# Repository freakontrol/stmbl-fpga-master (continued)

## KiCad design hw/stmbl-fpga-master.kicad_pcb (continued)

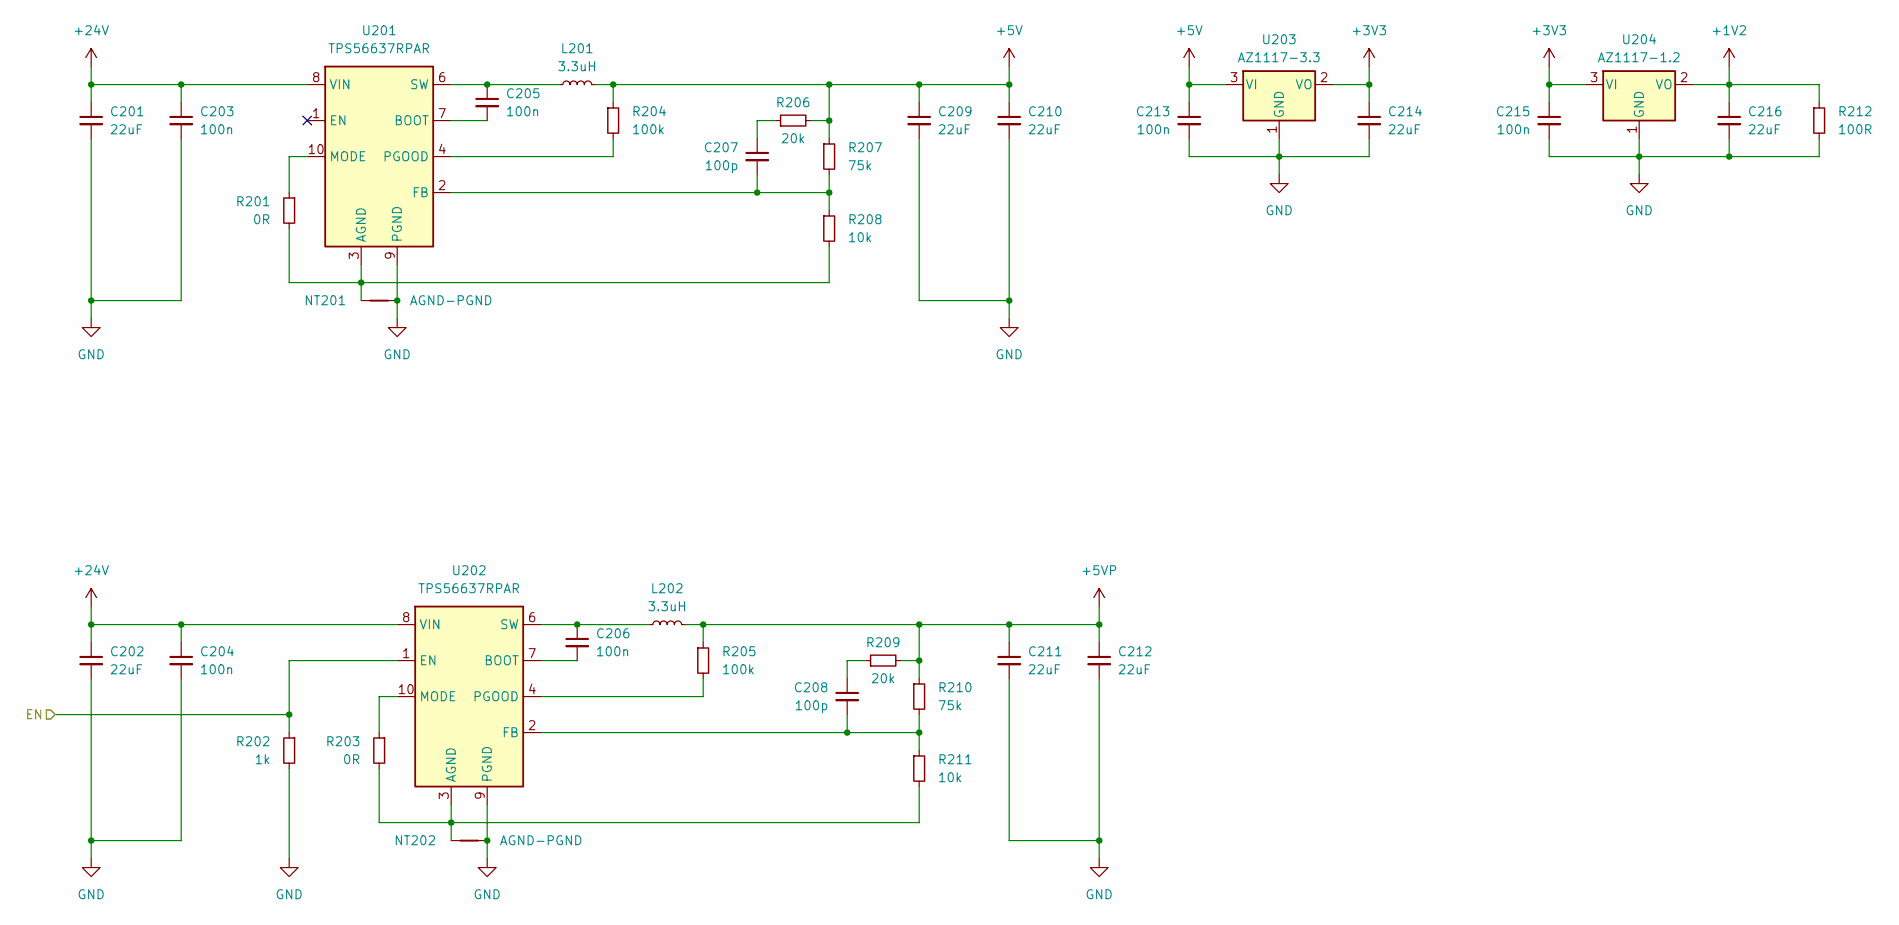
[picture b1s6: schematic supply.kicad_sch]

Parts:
C201, C202, C209, C210, C211, C212, C214, C216: 22uF; C_1206_3216Metric
C203, C204, C205, C206, C213, C215: 100n; C_0603_1608Metric
C207, C208: 100p; C_0603_1608Metric
L201, L202: 3.3uH; L_Sunlord_MWSA0603S
NT201, NT202: AGND-PGND; NetTie-2_SMD_Pad0.5mm
R201, R203: 0R; R_0603_1608Metric
R202: 1k; R_0603_1608Metric
R204, R205: 100k; R_0603_1608Metric
R206, R209: 20k; R_0603_1608Metric
R207, R210: 75k; R_0603_1608Metric
R208, R211: 10k; R_0603_1608Metric
R212: 100R; R_0603_1608Metric
U201, U202: TPS56637RPAR; Texas_RPA0010A_VQFN-HR-10_3x3mm_P0.5mm
U203: AZ1117-3.3; SOT-223-3_TabPin2
U204: AZ1117-1.2; SOT-223-3_TabPin2

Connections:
+1V2: C216.1, R212.1, U204.2 (VO); also elsewhere on the board
+3V3: C214.1, C215.1, U203.2 (VO), U204.3 (VI); also elsewhere on the board
+5V: C209.1, C210.1, C213.1, L201.2, R204.1, R206.2, R207.1, U203.3 (VI); also elsewhere on the board
+5VP: C211.1, C212.1, L202.2, R205.1, R209.2, R210.1; also elsewhere on the board
+24V: C201.1, C202.1, C203.1, C204.1, U201.8 (VIN), U202.8 (VIN); also elsewhere on the board
/FPGA Bank 2 3/EXT_PWR: R202.1, U202.1 (EN); also elsewhere on the board
GND: C201.2, C202.2, C203.2, C204.2, C209.2, C210.2, C211.2, C212.2, C213.2, C214.2, C215.2, C216.2, NT201.2, NT202.2, R202.2, R212.2, U201.9 (PGND), U202.9 (PGND), U203.1 (GND), U204.1 (GND); also elsewhere on the board
unnamed: C207.1, R206.1
unnamed: C208.1, R209.1
unnamed: NT201.1, R201.2, R208.2, U201.3 (AGND)
unnamed: C205.2, U201.7 (BOOT)
unnamed: C207.2, R207.2, R208.1, U201.2 (FB)
unnamed: R201.1, U201.10 (MODE)
unnamed: R204.2, U201.4 (PGOOD)
unnamed: C205.1, L201.1, U201.6 (SW)
unnamed: NT202.1, R203.2, R211.2, U202.3 (AGND)
unnamed: C206.2, U202.7 (BOOT)
unnamed: C208.2, R210.2, R211.1, U202.2 (FB)
unnamed: R203.1, U202.10 (MODE)
unnamed: R205.2, U202.4 (PGOOD)
unnamed: C206.1, L202.1, U202.6 (SW)

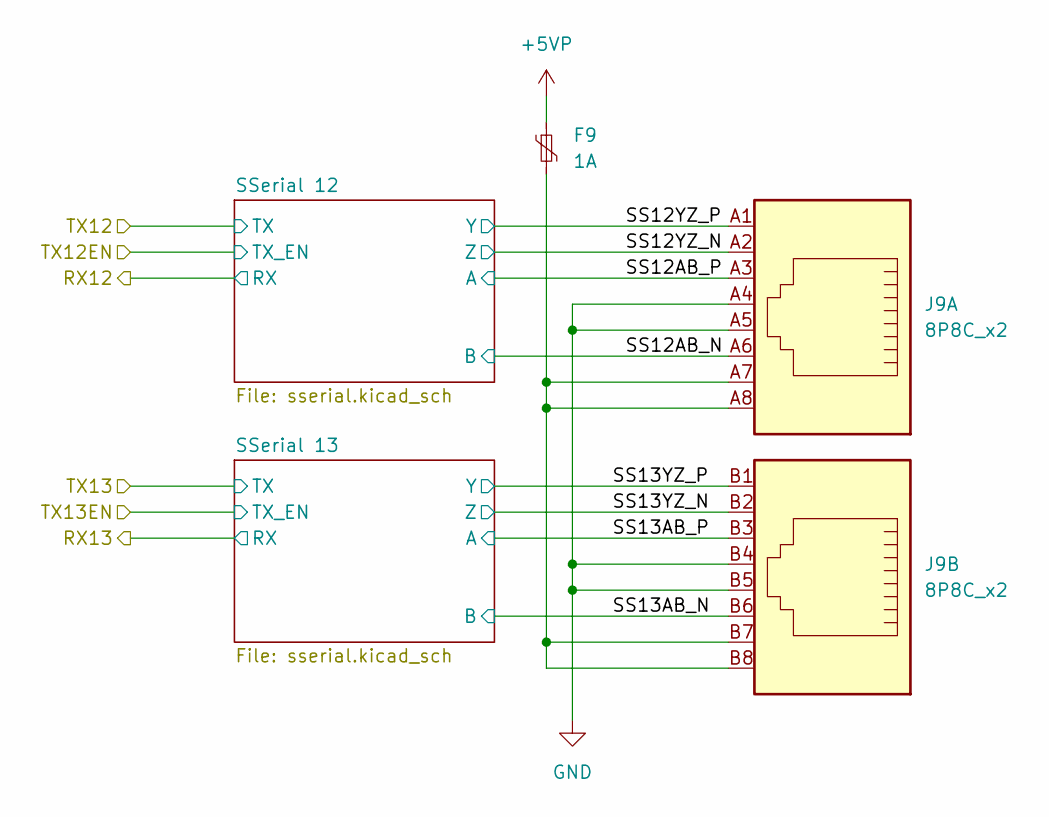
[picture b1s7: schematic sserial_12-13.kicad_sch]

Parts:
F9: 1A; Fuse_1206_3216Metric
J9: 8P8C_x2; HC-RJ45-5622-2-6

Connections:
+5VP: F9.1; also elsewhere on the board
/SSerial 12-13/SS12AB_N: J9.A6; also elsewhere on the board
/SSerial 12-13/SS12AB_P: J9.A3; also elsewhere on the board
/SSerial 12-13/SS12YZ_N: J9.A2; also elsewhere on the board
/SSerial 12-13/SS12YZ_P: J9.A1; also elsewhere on the board
/SSerial 12-13/SS13AB_N: J9.B6; also elsewhere on the board
/SSerial 12-13/SS13AB_P: J9.B3; also elsewhere on the board
/SSerial 12-13/SS13YZ_N: J9.B2; also elsewhere on the board
/SSerial 12-13/SS13YZ_P: J9.B1; also elsewhere on the board
GND: J9.A4, J9.A5, J9.B4, J9.B5; also elsewhere on the board
unnamed: F9.2, J9.A7, J9.A8, J9.B7, J9.B8

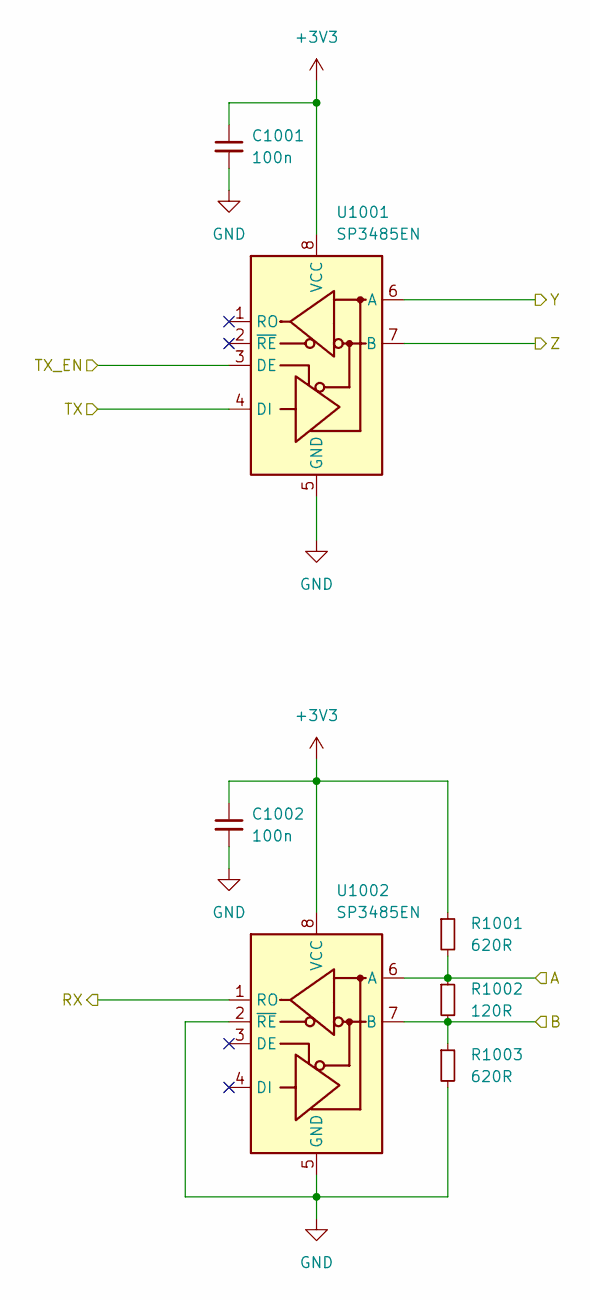
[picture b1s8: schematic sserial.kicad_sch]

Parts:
C1001, C1002: 100n; C_0603_1608Metric
R1001, R1003: 620R; R_0603_1608Metric
R1002: 120R; R_0603_1608Metric
U1001, U1002: SP3485EN; SOIC-8_3.9x4.9mm_P1.27mm

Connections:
+3V3: C1001.1, C1002.1, R1001.1, U1001.3 (DE), U1001.8 (VCC), U1002.8 (VCC); also elsewhere on the board
/FPGA Bank 2 3/RX0: U1002.1 (RO); also elsewhere on the board
/FPGA Bank 2 3/TX0: U1001.4 (DI); also elsewhere on the board
/SSerial 0-11/SS0AB_N: R1002.2, R1003.1, U1002.7 (B); also elsewhere on the board
/SSerial 0-11/SS0AB_P: R1001.2, R1002.1, U1002.6 (A); also elsewhere on the board
/SSerial 0-11/SS0YZ_N: U1001.7 (B); also elsewhere on the board
/SSerial 0-11/SS0YZ_P: U1001.6 (A); also elsewhere on the board
GND: C1001.2, C1002.2, R1003.2, U1001.5 (GND), U1002.2 (~RE), U1002.5 (GND); also elsewhere on the board

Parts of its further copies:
C1101, C1102, C1201, C1202, C1301, C1302, C1401, C1402, C1501, C1502, C1601, C1602, C1701, C1702, C1801, C1802, C1901, C1902, C2001, C2002, C2101, C2102, C2201, C2202, C2301, C2302: 100n; C_0603_1608Metric
R1101, R1103, R1201, R1203, R1301, R1303, R1401, R1403, R1501, R1503, R1601, R1603, R1701, R1703, R1801, R1803, R1901, R1903, R2001, R2003, R2101, R2103, R2201, R2203, R2301, R2303: 620R; R_0603_1608Metric
R1102, R1202, R1302, R1402, R1502, R1602, R1702, R1802, R1902, R2002, R2102, R2202, R2302: 120R; R_0603_1608Metric
U1101, U1102, U1201, U1202, U1301, U1302, U1401, U1402, U1501, U1502, U1601, U1602, U1701, U1702, U1801, U1802, U1901, U1902, U2001, U2002, U2101, U2102, U2201, U2202, U2301, U2302: SP3485EN; SOIC-8_3.9x4.9mm_P1.27mm

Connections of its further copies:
+3V3: C1101.1, C1102.1, C1201.1, C1202.1, C1301.1, C1302.1, C1401.1, C1402.1, C1501.1, C1502.1, C1601.1, C1602.1, C1701.1, C1702.1, C1801.1, C1802.1, C1901.1, C1902.1, C2001.1, C2002.1, C2101.1, C2102.1, C2201.1, C2202.1, C2301.1, C2302.1, R1101.1, R1201.1, R1301.1, R1401.1, R1501.1, R1601.1, R1701.1, R1801.1, R1901.1, R2001.1, R2101.1, R2201.1, R2301.1, U1101.3 (DE), U1101.8 (VCC), U1102.8 (VCC), U1201.3 (DE), U1201.8 (VCC), U1202.8 (VCC), U1301.3 (DE), U1301.8 (VCC), U1302.8 (VCC), U1401.3 (DE), U1401.8 (VCC), U1402.8 (VCC), U1501.3 (DE), U1501.8 (VCC), U1502.8 (VCC), U1601.3 (DE), U1601.8 (VCC), U1602.8 (VCC), U1701.3 (DE), U1701.8 (VCC), U1702.8 (VCC), U1801.3 (DE), U1801.8 (VCC), U1802.8 (VCC), U1901.3 (DE), U1901.8 (VCC), U1902.8 (VCC), U2001.3 (DE), U2001.8 (VCC), U2002.8 (VCC), U2101.3 (DE), U2101.8 (VCC), U2102.8 (VCC), U2201.8 (VCC), U2202.8 (VCC), U2301.8 (VCC), U2302.8 (VCC); also elsewhere on the board
/FPGA Bank 2 3/RX1: U1102.1 (RO); also elsewhere on the board
/FPGA Bank 2 3/RX2: U1202.1 (RO); also elsewhere on the board
/FPGA Bank 2 3/RX3: U1302.1 (RO); also elsewhere on the board
/FPGA Bank 2 3/RX4: U1402.1 (RO); also elsewhere on the board
/FPGA Bank 2 3/RX5: U1502.1 (RO); also elsewhere on the board
/FPGA Bank 2 3/RX6: U1602.1 (RO); also elsewhere on the board
/FPGA Bank 2 3/RX7: U1702.1 (RO); also elsewhere on the board
/FPGA Bank 2 3/RX8: U1802.1 (RO); also elsewhere on the board
/FPGA Bank 2 3/RX9: U1902.1 (RO); also elsewhere on the board
/FPGA Bank 2 3/RX10: U2002.1 (RO); also elsewhere on the board
/FPGA Bank 2 3/RX11: U2102.1 (RO); also elsewhere on the board
/FPGA Bank 2 3/RX12: U2202.1 (RO); also elsewhere on the board
/FPGA Bank 2 3/RX13: U2302.1 (RO); also elsewhere on the board
/FPGA Bank 2 3/TX1: U1101.4 (DI); also elsewhere on the board
/FPGA Bank 2 3/TX2: U1201.4 (DI); also elsewhere on the board
/FPGA Bank 2 3/TX3: U1301.4 (DI); also elsewhere on the board
/FPGA Bank 2 3/TX4: U1401.4 (DI); also elsewhere on the board
/FPGA Bank 2 3/TX5: U1501.4 (DI); also elsewhere on the board
/FPGA Bank 2 3/TX6: U1601.4 (DI); also elsewhere on the board
/FPGA Bank 2 3/TX7: U1701.4 (DI); also elsewhere on the board
/FPGA Bank 2 3/TX8: U1801.4 (DI); also elsewhere on the board
/FPGA Bank 2 3/TX9: U1901.4 (DI); also elsewhere on the board
/FPGA Bank 2 3/TX10: U2001.4 (DI); also elsewhere on the board
/FPGA Bank 2 3/TX11: U2101.4 (DI); also elsewhere on the board
/FPGA Bank 2 3/TX12: U2201.4 (DI); also elsewhere on the board
/FPGA Bank 2 3/TX12EN: U2201.3 (DE); also elsewhere on the board
/FPGA Bank 2 3/TX13: U2301.4 (DI); also elsewhere on the board
/FPGA Bank 2 3/TX13EN: U2301.3 (DE); also elsewhere on the board
/SSerial 0-11/SS1AB_N: R1102.2, R1103.1, U1102.7 (B); also elsewhere on the board
/SSerial 0-11/SS1AB_P: R1101.2, R1102.1, U1102.6 (A); also elsewhere on the board
/SSerial 0-11/SS1YZ_N: U1101.7 (B); also elsewhere on the board
/SSerial 0-11/SS1YZ_P: U1101.6 (A); also elsewhere on the board
/SSerial 0-11/SS2AB_N: R1202.2, R1203.1, U1202.7 (B); also elsewhere on the board
/SSerial 0-11/SS2AB_P: R1201.2, R1202.1, U1202.6 (A); also elsewhere on the board
/SSerial 0-11/SS2YZ_N: U1201.7 (B); also elsewhere on the board
/SSerial 0-11/SS2YZ_P: U1201.6 (A); also elsewhere on the board
/SSerial 0-11/SS3AB_N: R1302.2, R1303.1, U1302.7 (B); also elsewhere on the board
/SSerial 0-11/SS3AB_P: R1301.2, R1302.1, U1302.6 (A); also elsewhere on the board
/SSerial 0-11/SS3YZ_N: U1301.7 (B); also elsewhere on the board
/SSerial 0-11/SS3YZ_P: U1301.6 (A); also elsewhere on the board
/SSerial 0-11/SS4AB_N: R1402.2, R1403.1, U1402.7 (B); also elsewhere on the board
/SSerial 0-11/SS4AB_P: R1401.2, R1402.1, U1402.6 (A); also elsewhere on the board
/SSerial 0-11/SS4YZ_N: U1401.7 (B); also elsewhere on the board
/SSerial 0-11/SS4YZ_P: U1401.6 (A); also elsewhere on the board
/SSerial 0-11/SS5AB_N: R1502.2, R1503.1, U1502.7 (B); also elsewhere on the board
/SSerial 0-11/SS5AB_P: R1501.2, R1502.1, U1502.6 (A); also elsewhere on the board
/SSerial 0-11/SS5YZ_N: U1501.7 (B); also elsewhere on the board
/SSerial 0-11/SS5YZ_P: U1501.6 (A); also elsewhere on the board
/SSerial 0-11/SS6AB_N: R1602.2, R1603.1, U1602.7 (B); also elsewhere on the board
/SSerial 0-11/SS6AB_P: R1601.2, R1602.1, U1602.6 (A); also elsewhere on the board
/SSerial 0-11/SS6YZ_N: U1601.7 (B); also elsewhere on the board
/SSerial 0-11/SS6YZ_P: U1601.6 (A); also elsewhere on the board
/SSerial 0-11/SS7AB_N: R1702.2, R1703.1, U1702.7 (B); also elsewhere on the board
/SSerial 0-11/SS7AB_P: R1701.2, R1702.1, U1702.6 (A); also elsewhere on the board
/SSerial 0-11/SS7YZ_N: U1701.7 (B); also elsewhere on the board
/SSerial 0-11/SS7YZ_P: U1701.6 (A); also elsewhere on the board
/SSerial 0-11/SS8AB_N: R1802.2, R1803.1, U1802.7 (B); also elsewhere on the board
/SSerial 0-11/SS8AB_P: R1801.2, R1802.1, U1802.6 (A); also elsewhere on the board
/SSerial 0-11/SS8YZ_N: U1801.7 (B); also elsewhere on the board
/SSerial 0-11/SS8YZ_P: U1801.6 (A); also elsewhere on the board
/SSerial 0-11/SS9AB_N: R1902.2, R1903.1, U1902.7 (B); also elsewhere on the board
/SSerial 0-11/SS9AB_P: R1901.2, R1902.1, U1902.6 (A); also elsewhere on the board
/SSerial 0-11/SS9YZ_N: U1901.7 (B); also elsewhere on the board
/SSerial 0-11/SS9YZ_P: U1901.6 (A); also elsewhere on the board
/SSerial 0-11/SS10AB_N: R2002.2, R2003.1, U2002.7 (B); also elsewhere on the board
/SSerial 0-11/SS10AB_P: R2001.2, R2002.1, U2002.6 (A); also elsewhere on the board
/SSerial 0-11/SS10YZ_N: U2001.7 (B); also elsewhere on the board
/SSerial 0-11/SS10YZ_P: U2001.6 (A); also elsewhere on the board
/SSerial 0-11/SS11AB_N: R2102.2, R2103.1, U2102.7 (B); also elsewhere on the board
/SSerial 0-11/SS11AB_P: R2101.2, R2102.1, U2102.6 (A); also elsewhere on the board
/SSerial 0-11/SS11YZ_N: U2101.7 (B); also elsewhere on the board
/SSerial 0-11/SS11YZ_P: U2101.6 (A); also elsewhere on the board
/SSerial 12-13/SS12AB_N: R2202.2, R2203.1, U2202.7 (B); also elsewhere on the board
/SSerial 12-13/SS12AB_P: R2201.2, R2202.1, U2202.6 (A); also elsewhere on the board
/SSerial 12-13/SS12YZ_N: U2201.7 (B); also elsewhere on the board
/SSerial 12-13/SS12YZ_P: U2201.6 (A); also elsewhere on the board
/SSerial 12-13/SS13AB_N: R2302.2, R2303.1, U2302.7 (B); also elsewhere on the board
/SSerial 12-13/SS13AB_P: R2301.2, R2302.1, U2302.6 (A); also elsewhere on the board
/SSerial 12-13/SS13YZ_N: U2301.7 (B); also elsewhere on the board
/SSerial 12-13/SS13YZ_P: U2301.6 (A); also elsewhere on the board
GND: C1101.2, C1102.2, C1201.2, C1202.2, C1301.2, C1302.2, C1401.2, C1402.2, C1501.2, C1502.2, C1601.2, C1602.2, C1701.2, C1702.2, C1801.2, C1802.2, C1901.2, C1902.2, C2001.2, C2002.2, C2101.2, C2102.2, C2201.2, C2202.2, C2301.2, C2302.2, R1103.2, R1203.2, R1303.2, R1403.2, R1503.2, R1603.2, R1703.2, R1803.2, R1903.2, R2003.2, R2103.2, R2203.2, R2303.2, U1101.5 (GND), U1102.2 (~RE), U1102.5 (GND), U1201.5 (GND), U1202.2 (~RE), U1202.5 (GND), U1301.5 (GND), U1302.2 (~RE), U1302.5 (GND), U1401.5 (GND), U1402.2 (~RE), U1402.5 (GND), U1501.5 (GND), U1502.2 (~RE), U1502.5 (GND), U1601.5 (GND), U1602.2 (~RE), U1602.5 (GND), U1701.5 (GND), U1702.2 (~RE), U1702.5 (GND), U1801.5 (GND), U1802.2 (~RE), U1802.5 (GND), U1901.5 (GND), U1902.2 (~RE), U1902.5 (GND), U2001.5 (GND), U2002.2 (~RE), U2002.5 (GND), U2101.5 (GND), U2102.2 (~RE), U2102.5 (GND), U2201.5 (GND), U2202.2 (~RE), U2202.5 (GND), U2301.5 (GND), U2302.2 (~RE), U2302.5 (GND); also elsewhere on the board

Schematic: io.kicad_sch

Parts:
C2401: 100n; C_0603_1608Metric
F4: 1A; Fuse_1206_3216Metric
J4: Parallel expansion port; IDC-Header_2x13_P2.54mm_Horizontal
JP41: IO Voltage; SolderJumper-3_P1.3mm_Bridged12_RoundedPad1.0x1.5mm
JP42: PULL-UP/DOWN; SolderJumper-3_P1.3mm_Bridged12_RoundedPad1.0x1.5mm
JP43: Breakout Power; SolderJumper-3_P1.3mm_Bridged12_RoundedPad1.0x1.5mm
Q2401: SS8550; SOT-23
R2401, R2402: 1k; R_0603_1608Metric
R2403: 4k99; R_0603_1608Metric
R2404: 4k7; R_0603_1608Metric
RN2401, RN2402, RN2403, RN2404: 4k7; R_Array_Convex_4x0603
U2401: 74CB3T16210DGG; TSSOP-48_6.1x12.5mm_P0.5mm

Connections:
+3V3: JP41.3 (B); also elsewhere on the board
+5V: JP41.1 (A), Q2401.2 (E), R2402.1; also elsewhere on the board
+5VP: F4.1; also elsewhere on the board
/FPGA Bank 0 1/Parallel expansion port/FPGA_IO0: U2401.5 (1A4); also elsewhere on the board
/FPGA Bank 0 1/Parallel expansion port/FPGA_IO1: U2401.6 (1A5); also elsewhere on the board
/FPGA Bank 0 1/Parallel expansion port/FPGA_IO2: U2401.7 (1A6); also elsewhere on the board
/FPGA Bank 0 1/Parallel expansion port/FPGA_IO3: U2401.9 (1A7); also elsewhere on the board
/FPGA Bank 0 1/Parallel expansion port/FPGA_IO4: U2401.10 (1A8); also elsewhere on the board
/FPGA Bank 0 1/Parallel expansion port/FPGA_IO5: U2401.11 (1A9); also elsewhere on the board
/FPGA Bank 0 1/Parallel expansion port/FPGA_IO6: U2401.12 (1A10); also elsewhere on the board
/FPGA Bank 0 1/Parallel expansion port/FPGA_IO7: U2401.13 (2A1); also elsewhere on the board
/FPGA Bank 0 1/Parallel expansion port/FPGA_IO8: U2401.14 (2A2); also elsewhere on the board
/FPGA Bank 0 1/Parallel expansion port/FPGA_IO9: U2401.16 (2A3); also elsewhere on the board
/FPGA Bank 0 1/Parallel expansion port/FPGA_IO10: U2401.18 (2A4); also elsewhere on the board
/FPGA Bank 0 1/Parallel expansion port/FPGA_IO11: U2401.19 (2A5); also elsewhere on the board
/FPGA Bank 0 1/Parallel expansion port/FPGA_IO12: U2401.20 (2A6); also elsewhere on the board
/FPGA Bank 0 1/Parallel expansion port/FPGA_IO13: U2401.21 (2A7); also elsewhere on the board
/FPGA Bank 0 1/Parallel expansion port/FPGA_IO14: U2401.22 (2A8); also elsewhere on the board
/FPGA Bank 0 1/Parallel expansion port/FPGA_IO15: U2401.23 (2A9); also elsewhere on the board
/FPGA Bank 0 1/Parallel expansion port/FPGA_IO16: U2401.24 (2A10); also elsewhere on the board
/FPGA Bank 0 1/Parallel expansion port/IO0: J4.1, RN2401.4 (R4.1), U2401.43 (1B4)
/FPGA Bank 0 1/Parallel expansion port/IO1: J4.2, RN2401.3 (R3.1), U2401.42 (1B5)
/FPGA Bank 0 1/Parallel expansion port/IO2: J4.3, RN2401.2 (R2.1), U2401.40 (1B6)
/FPGA Bank 0 1/Parallel expansion port/IO3: J4.4, RN2401.1 (R1.1), U2401.39 (1B7)
/FPGA Bank 0 1/Parallel expansion port/IO4: J4.5, RN2402.4 (R4.1), U2401.38 (1B8)
/FPGA Bank 0 1/Parallel expansion port/IO5: J4.6, RN2402.3 (R3.1), U2401.37 (1B9)
/FPGA Bank 0 1/Parallel expansion port/IO6: J4.7, RN2402.2 (R2.1), U2401.36 (1B10)
/FPGA Bank 0 1/Parallel expansion port/IO7: J4.8, RN2402.1 (R1.1), U2401.35 (2B1)
/FPGA Bank 0 1/Parallel expansion port/IO8: J4.9, RN2403.1 (R1.1), U2401.34 (2B2)
/FPGA Bank 0 1/Parallel expansion port/IO9: J4.11, RN2403.2 (R2.1), U2401.33 (2B3)
/FPGA Bank 0 1/Parallel expansion port/IO10: J4.13, RN2403.3 (R3.1), U2401.31 (2B4)
/FPGA Bank 0 1/Parallel expansion port/IO11: J4.15, RN2403.4 (R4.1), U2401.30 (2B5)
/FPGA Bank 0 1/Parallel expansion port/IO12: J4.17, RN2404.1 (R1.1), U2401.29 (2B6)
/FPGA Bank 0 1/Parallel expansion port/IO13: J4.19, RN2404.2 (R2.1), U2401.28 (2B7)
/FPGA Bank 0 1/Parallel expansion port/IO14: J4.21, RN2404.3 (R3.1), U2401.27 (2B8)
/FPGA Bank 0 1/Parallel expansion port/IO15: J4.23, RN2404.4 (R4.1), U2401.26 (2B9)
/FPGA Bank 0 1/Parallel expansion port/IO16: J4.25, R2404.2, U2401.25 (2B10)
GND: C2401.2, J4.10, J4.12, J4.14, J4.16, JP42.3 (B), JP43.3 (B), R2403.2, U2401.8 (GND), U2401.17 (GND), U2401.32 (GND), U2401.41 (GND), U2401.47 (2~OE), U2401.48 (1~OE); also elsewhere on the board
unnamed: J4.18, J4.20, J4.22, J4.24, J4.26, JP43.2 (C)
unnamed: JP41.2 (C), JP42.1 (A), R2401.1
unnamed: JP42.2 (C), R2404.1, RN2401.5 (R4.2), RN2401.6 (R3.2), RN2401.7 (R2.2), RN2401.8 (R1.2), RN2402.5 (R4.2), RN2402.6 (R3.2), RN2402.7 (R2.2), RN2402.8 (R1.2), RN2403.5 (R4.2), RN2403.6 (R3.2), RN2403.7 (R2.2), RN2403.8 (R1.2), RN2404.5 (R4.2), RN2404.6 (R3.2), RN2404.7 (R2.2), RN2404.8 (R1.2)
unnamed: F4.2, JP43.1 (A)
unnamed: Q2401.1 (B), R2401.2
unnamed: C2401.1, Q2401.3 (C), R2402.2, R2403.1, U2401.15 (VCC)

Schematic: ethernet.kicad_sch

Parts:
C601, C603, C610, C611: 4.7uF; C_0603_1608Metric
C602, C604, C605, C606, C607, C608, C609, C612, C613, C614, C615: 100n; C_0603_1608Metric
J5: Ethernet; RJ45_Hanrun_HR911105A_Horizontal
L601, L602, L603: 100R@100MHz; L_0805_2012Metric
R601: 1k; R_0603_1608Metric
R602, R611: 10k; R_0603_1608Metric
R603: 3k01 1%; R_0603_1608Metric
R604, R605, R610: 300R; R_0603_1608Metric
R606, R607, R608, R609: 49R9 1%; R_0603_1608Metric
RN601, RN602: 1k; R_Array_Convex_4x0603
U601: KSZ8851-16MLL; LQFP-48_7x7mm_P0.5mm
U602: 93LC46B/SN; SOIC-8_3.9x4.9mm_P1.27mm

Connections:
+3V3: C601.1, C602.1, C604.1, C606.1, C613.1, J5.9, J5.12, L601.1, R601.1, R611.1, U601.27 (VDD_IO), U601.38 (VDD_IO), U601.46 (VDD_IO), U602.6 (ORG), U602.8 (VCC); also elsewhere on the board
/FPGA Bank 0 1/Ethernet/CLOCK: U601.24 (X1); also elsewhere on the board
/FPGA Bank 0 1/Ethernet/CMD: U601.11 (CMD); also elsewhere on the board
/FPGA Bank 0 1/Ethernet/CS: U601.15 (EECS), U602.1 (CS)
/FPGA Bank 0 1/Ethernet/DIO: R610.1, R611.2, U601.9 (EDD_IO), U602.3 (DI)
/FPGA Bank 0 1/Ethernet/SCLK: U601.10 (EESK), U602.2 (SCLK)
/FPGA Bank 0 1/Ethernet/SD0: U601.48 (SD0); also elsewhere on the board
/FPGA Bank 0 1/Ethernet/SD1: U601.47 (SD1); also elsewhere on the board
/FPGA Bank 0 1/Ethernet/SD2: U601.45 (SD2); also elsewhere on the board
/FPGA Bank 0 1/Ethernet/SD3: U601.44 (SD3); also elsewhere on the board
/FPGA Bank 0 1/Ethernet/SD4: U601.43 (SD4); also elsewhere on the board
/FPGA Bank 0 1/Ethernet/SD5: U601.42 (SD5); also elsewhere on the board
/FPGA Bank 0 1/Ethernet/SD6: U601.41 (SD6); also elsewhere on the board
/FPGA Bank 0 1/Ethernet/SD7: U601.40 (SD7); also elsewhere on the board
/FPGA Bank 0 1/Ethernet/SD8: RN602.6 (R3.2), U601.39 (SD8); also elsewhere on the board
/FPGA Bank 0 1/Ethernet/SD9: RN601.8 (R1.2), U601.36 (SD9); also elsewhere on the board
/FPGA Bank 0 1/Ethernet/SD10: RN602.5 (R4.2), U601.35 (SD10); also elsewhere on the board
/FPGA Bank 0 1/Ethernet/SD11: RN601.5 (R4.2), U601.34 (SD11); also elsewhere on the board
/FPGA Bank 0 1/Ethernet/SD12: RN602.7 (R2.2), U601.33 (SD12); also elsewhere on the board
/FPGA Bank 0 1/Ethernet/SD13: RN601.6 (R3.2), U601.32 (SD13); also elsewhere on the board
/FPGA Bank 0 1/Ethernet/SD14: RN602.8 (R1.2), U601.31 (SD14); also elsewhere on the board
/FPGA Bank 0 1/Ethernet/SD15: RN601.7 (R2.2), U601.30 (SD15); also elsewhere on the board
/FPGA Bank 0 1/Ethernet/~CS: U601.12 (~CS); also elsewhere on the board
/FPGA Bank 0 1/Ethernet/~INTR: R601.2, U601.4 (~INTR); also elsewhere on the board
/FPGA Bank 0 1/Ethernet/~RD: U601.5 (~RD); also elsewhere on the board
/FPGA Bank 0 1/Ethernet/~RST: R602.1, U601.23 (~RST); also elsewhere on the board
/FPGA Bank 0 1/Ethernet/~WR: U601.6 (~WR); also elsewhere on the board
GND: C601.2, C602.2, C603.2, C604.2, C605.2, C606.2, C607.2, C608.2, C609.2, C610.2, C611.2, C612.2, C613.2, C614.2, C615.2, L603.2, R602.2, R603.2, RN601.1 (R1.1), RN601.2 (R2.1), RN601.3 (R3.1), RN601.4 (R4.1), RN602.1 (R1.1), RN602.2 (R2.1), RN602.3 (R3.1), RN602.4 (R4.1), U601.7 (DGND), U601.13 (AGND), U601.18 (AGND), U601.26 (DGND), U601.28 (DGND), U601.37 (DGND), U602.5 (GND); also elsewhere on the board
GNDS: J5.8, J5.SH, L603.1
unnamed: C612.1, R606.2, R607.2
unnamed: C614.1, R608.2, R609.2
unnamed: J5.10, R604.2
unnamed: J5.11, R605.2
unnamed: C603.1, C605.1, C615.1, J5.4 (TCT), J5.5 (RCT), L601.2, U601.21 (VDD_A3.3)
unnamed: J5.3 (RD+), R608.1, U601.16 (RXP1)
unnamed: J5.6 (RD-), R609.1, U601.17 (PXM1)
unnamed: J5.1 (TD+), R606.1, U601.19 (TXP1)
unnamed: J5.2 (TD-), R607.1, U601.20 (TXM1)
unnamed: R603.1, U601.22 (ISET)
unnamed: R604.1, U601.2 (P1LED0)
unnamed: R605.1, U601.1 (P1LED1)
unnamed: C609.1, C611.1, L602.1, U601.14 (VDD_A1.8)
unnamed: C607.1, C608.1, C610.1, L602.2, U601.8 (VDD_CO1.8), U601.29 (VDD_D1.8)
unnamed: R610.2, U602.4 (DO)

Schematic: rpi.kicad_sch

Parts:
C701, C702, C703: 100n; C_0603_1608Metric
JP2: HAT EEPROM WP; SolderJumper-2_P1.3mm_Open_RoundedPad1.0x1.5mm
R701, R702: 3k9; R_0603_1608Metric
R703: 1k; R_0603_1608Metric
U2: RaspberryPi-4/5; Raspberry_Pi_5_Socketed_THT_FaceDown_MountingHoles
U701: 24LC32AT-x/OT; SOT-23-5

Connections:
+3V3: C703.1, R701.1, R702.1, R703.1, U701.4 (VCC); also elsewhere on the board
+5V: U2.2 (5V), U2.4 (5V); also elsewhere on the board
/FPGA Bank 2 3/Raspberry Pi/RX: U2.10 (GPIO15/RXD); also elsewhere on the board
/FPGA Bank 2 3/Raspberry Pi/SCL: U2.5 (SCL/GPIO3); also elsewhere on the board
/FPGA Bank 2 3/Raspberry Pi/SCLK: U2.23 (SCLK0/GPIO11); also elsewhere on the board
/FPGA Bank 2 3/Raspberry Pi/SDA: U2.3 (SDA/GPIO2); also elsewhere on the board
/FPGA Bank 2 3/Raspberry Pi/SPICS: U2.24 (~CE0/GPIO8); also elsewhere on the board
/FPGA Bank 2 3/Raspberry Pi/SPIIN: U2.21 (MISO0/GPIO9); also elsewhere on the board
/FPGA Bank 2 3/Raspberry Pi/SPIOUT: U2.19 (MOSI0/GPIO10); also elsewhere on the board
/FPGA Bank 2 3/Raspberry Pi/TX: U2.8 (GPIO14/TXD); also elsewhere on the board
GND: C701.2, C702.2, C703.2, JP2.1 (A), U2.6 (GND), U2.9 (GND), U2.14 (GND), U2.20 (GND), U2.25 (GND), U2.30 (GND), U2.34 (GND), U2.39 (GND), U701.2 (GND); also elsewhere on the board
unnamed: C701.1, U2.17 (3V3)
unnamed: C702.1, U2.1 (3V3)
unnamed: JP2.2 (B), R703.2, U701.5 (WP)
unnamed: R702.2, U2.28 (ID_SC/GPIO1), U701.1 (SCL)
unnamed: R701.2, U2.27 (ID_SD/GPIO0), U701.3 (SDA)

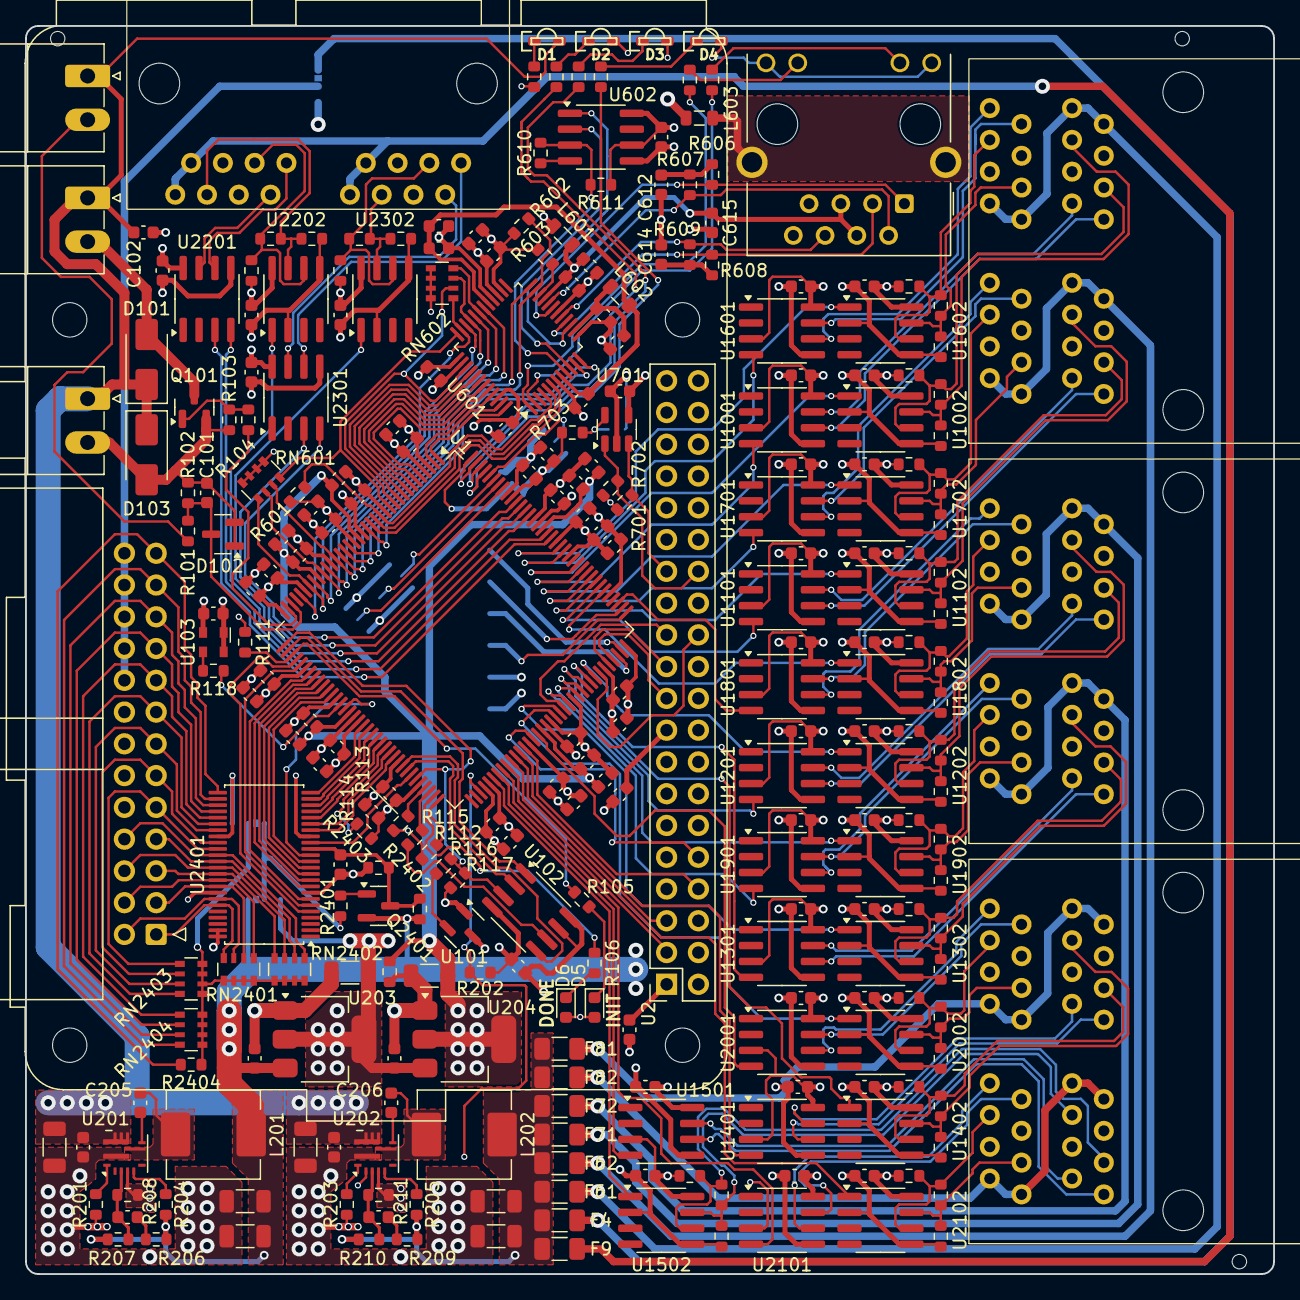
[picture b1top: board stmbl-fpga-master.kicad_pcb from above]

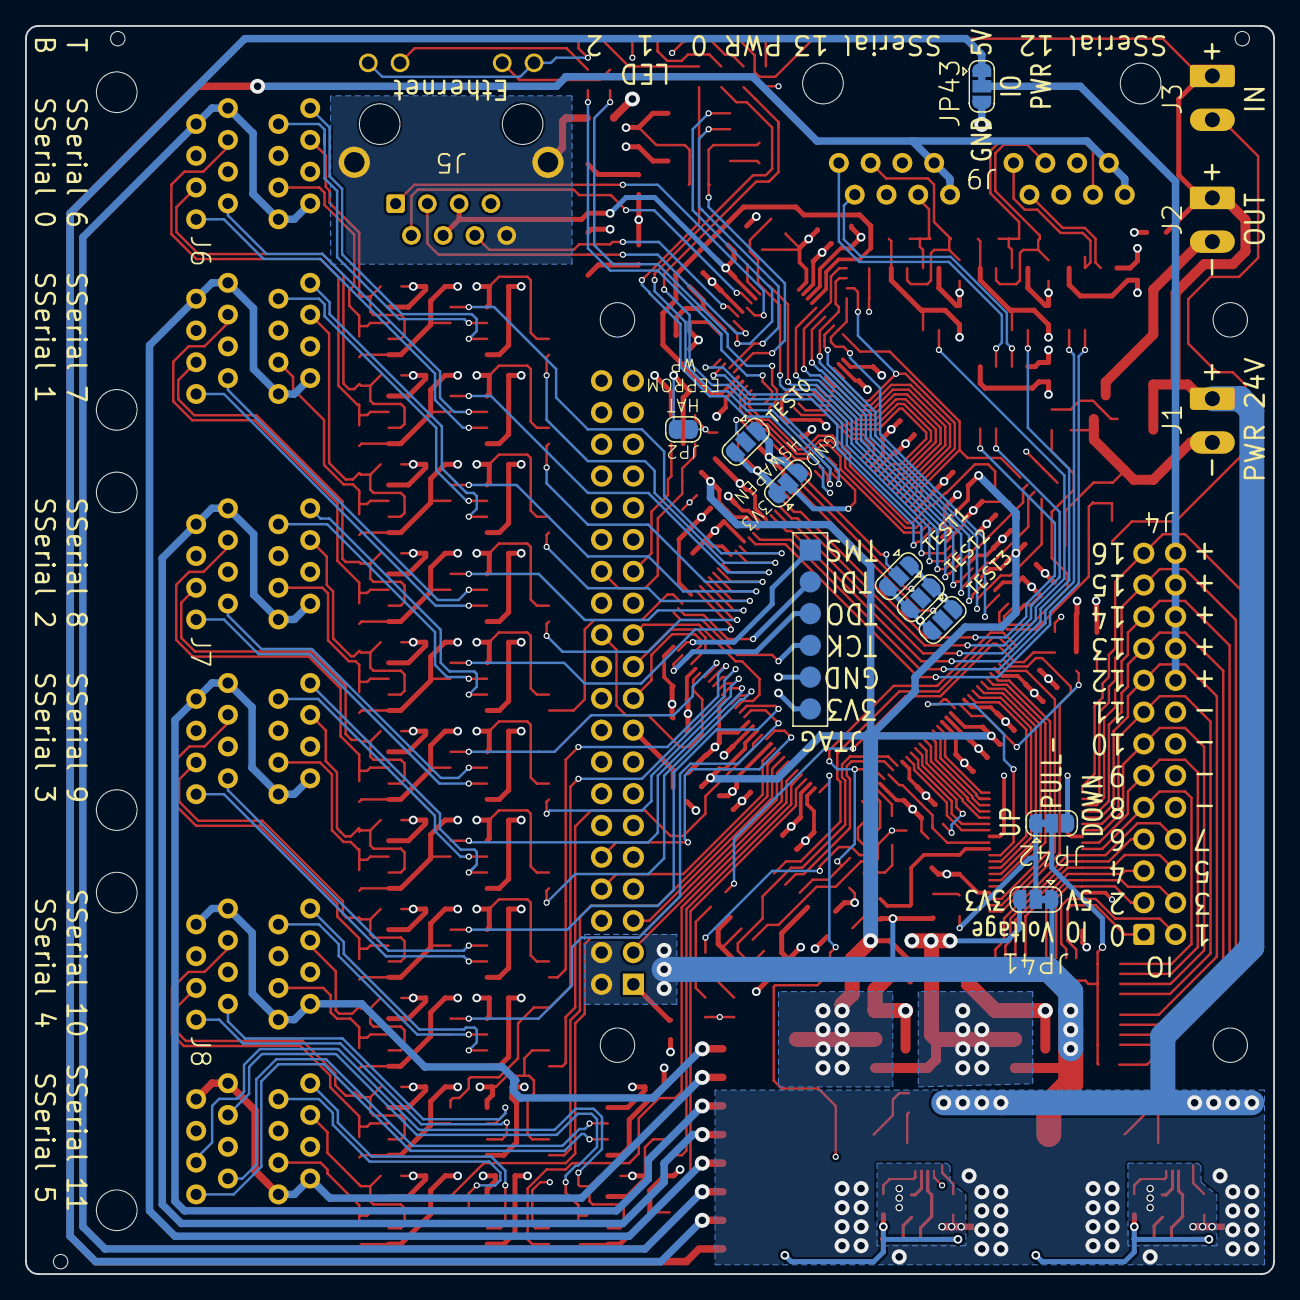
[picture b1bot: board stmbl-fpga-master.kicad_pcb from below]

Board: 4 copper layers, 99.8 x 99.8 mm, 284 parts (10 on the bottom side), 246 nets.

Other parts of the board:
TEST0, TEST1, TEST2, TEST3: SolderJumper-3_P1.3mm_Open_RoundedPad1.0x1.5mm

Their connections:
+3V3: TEST0.3 (B), TEST1.3 (B), TEST2.3 (B), TEST3.3 (B); also elsewhere on the board
/FPGA Bank 2 3/TEST0: TEST0.2 (C); also elsewhere on the board
/FPGA Bank 2 3/TEST1: TEST1.2 (C); also elsewhere on the board
/FPGA Bank 2 3/TEST2: TEST2.2 (C); also elsewhere on the board
/FPGA Bank 2 3/TEST3: TEST3.2 (C); also elsewhere on the board
GND: TEST0.1 (A), TEST1.1 (A), TEST2.1 (A), TEST3.1 (A); also elsewhere on the board

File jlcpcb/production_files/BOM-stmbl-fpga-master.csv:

Comment,Designator,Footprint,LCSC,Quantity
100R@100MHz,"L601,L602,L603",L_0805_2012Metric,C1015,3
SMAJ24A,D103,D_SMA,C113962,1
Ethernet,J5,RJ45_Hanrun_HR911105A_Horizontal,C12074,1
22uF,"C201,C202,C209,C210,C211,C212,C214,C216",C_1206_3216Metric,C12891,8
93LC46B/SN,U602,SOIC-8_3.9x4.9mm_P1.27mm,C1348804,1
100n,"C1001,C1002,C102,C1101,C1102,C1201,C1202,C1301,C1302,C133,C136,C1401,C1402,C1501,C1502,C1601,C1602,C1701,C1702,C1801,C1802,C1901,C1902,C2001,C2002,C203,C204,C205,C206,C2101,C2102,C213,C215,C2201,C2202,C2301,C2302,C2401,C602,C604,C605,C606,C607,C608,C609,C612,C613,C614,C615,C701,C702,C703",C_0603_1608Metric,C14663,52
100p,"C207,C208",C_0603_1608Metric,C14858,2
1n,C101,C_0603_1608Metric,C1588,1
yellow,D3,LED-0805-SIDE,C160468,1
POWER,"D1,D2",LED-0805-SIDE,C160469,2
470n,"C104,C105,C106,C107,C108,C112,C113,C114,C115,C116,C117,C124,C125,C126,C127,C128,C129,C130,C131,C132,C134",C_0603_1608Metric,C1623,21
4.7uF,"C103,C109,C110,C111,C118,C119,C120,C121,C122,C123,C135,C137,C138,C139,C601,C603,C610,C611",C_0603_1608Metric,C19666,18
4k7,"RN2401,RN2402,RN2403,RN2404",R_Array_Convex_4x0603,C1980,4
1k,"RN601,RN602",R_Array_Convex_4x0603,C20197,2
AO3400A,Q101,SOT-23,C20917,1
Parallel expansion port,J4,IDC-Header_2x13_P2.54mm_Horizontal,C21167,1
0R,"R201,R203",R_0603_1608Metric,C21189,2
1k,"R102,R103,R105,R106,R107,R108,R109,R111,R112,R113,R114,R117,R202,R2401,R2402,R601,R703",R_0603_1608Metric,C21190,17
100R,R212,R_0603_1608Metric,C22775,1
120R,"R1002,R1102,R1202,R1302,R1402,R1502,R1602,R1702,R1802,R1902,R2002,R2102,R2202,R2302",R_0603_1608Metric,C22787,14
INIT,"D5,D6",LED_0603_1608Metric,C2286,2
3k9,"R110,R701,R702",R_0603_1608Metric,C23018,3
300R,"R116,R604,R605,R610",R_0603_1608Metric,C23025,4
4k99,R2403,R_0603_1608Metric,C23046,1
4k7,R2404,R_0603_1608Metric,C23162,1
49.9R,"R115,R118,R606,R607,R608,R609",R_0603_1608Metric,C23185,6
620R,"R1001,R1003,R1101,R1103,R1201,R1203,R1301,R1303,R1401,R1403,R1501,R1503,R1601,R1603,R1701,R1703,R1801,R1803,R1901,R1903,R2001,R2003,R2101,R2103,R2201,R2203,R2301,R2303",R_0603_1608Metric,C23228,28
75k,"R207,R210",R_0603_1608Metric,C23242,2
22R,R104,R_0603_1608Metric,C23345,1
W25Q16JVSn,U102,SOIC-8_3.9x4.9mm_P1.27mm,C2456211,1
100k,"R204,R205",R_0603_1608Metric,C25803,2
10k,"R101,R208,R211,R602,R611",R_0603_1608Metric,C25804,5
74CB3T16210DGG,U2401,TSSOP-48_6.1x12.5mm_P0.5mm,C2674635,1
1A,"F4,F61,F62,F71,F72,F81,F82,F9",Fuse_1206_3216Metric,C2830246,8
red,D4,LED-0805-SIDE,C284935,1
8P8C_x2,J9,HC-RJ45-5622-2-6,C3010552,1
SM712_SOT23,D102,SOT-23,C32677,1
AZ1117-1.2,U204,SOT-223-3_TabPin2,C347218,1
3.3uH,"L201,L202",L_Sunlord_MWSA0603S,C408446,2
US1M,D101,D_SMA,C412437,1
XC6SLX9-TQG144,U1,TQFP-144_20x20mm_P0.5mm,C415799,1
20k,"R206,R209",R_0603_1608Metric,C4184,2
3k01 1%,R603,R_0603_1608Metric,C4211,1
8P8C_x4,"J6,J7,J8",MJ5988-B022-HPRN1,C501474,3
ASDMB-50MHz,U103,Oscillator_SMD_Abracon_ASDMB-4Pin_2.5x2.0mm,C596948,1
24LC32AT-x/OT,U701,SOT-23-5,C616245,1
AZ1117-3.3,U203,SOT-223-3_TabPin2,C6186,1
KSZ8851-16MLL,U601,LQFP-48_7x7mm_P0.5mm,C631669,1
TPS56637RPAR,"U201,U202",Texas_RPA0010A_VQFN-HR-10_3x3mm_P0.5mm,C841386,2
LM809,U101,SOT-23,C85255,1
SS8550,Q2401,SOT-23,C8542,1
SP3485EN,"U1001,U1002,U1101,U1102,U1201,U1202,U1301,U1302,U1401,U1402,U1501,U1502,U1601,U1602,U1701,U1702,U1801,U1802,U1901,U1902,U2001,U2002,U2101,U2102,U2201,U2202,U2301,U2302",SOIC-8_3.9x4.9mm_P1.27mm,C8963,28

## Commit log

2025-02-01 added hostmot2 firmware source from mesanet
2025-02-09 schematic
2025-02-16 fixed some stuff
2025-03-09 some changes in schematic and added pcb
2025-03-09 jlcpcb production files
2025-03-09 xilinx ise gitignore
2025-03-09 hostmot2 firmware
2025-03-09 Create LICENSE
2025-03-16 added hugo-book submodule
2025-03-16 readme and docs
2025-03-16 updated 3d models
2025-03-16 setname script
2025-03-16 hostmot2 bit files
2025-03-16 github pages workflow
2025-03-16 fixed images
2025-07-15 updated wrong traces on kicad_pcb
2025-07-20 Added 3D case step and source
